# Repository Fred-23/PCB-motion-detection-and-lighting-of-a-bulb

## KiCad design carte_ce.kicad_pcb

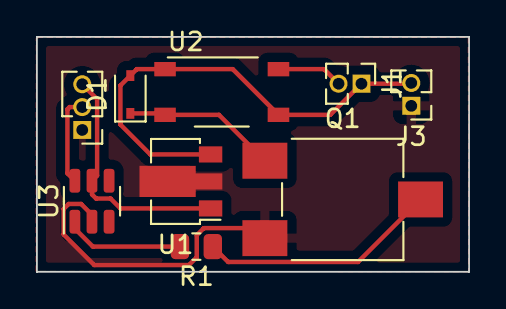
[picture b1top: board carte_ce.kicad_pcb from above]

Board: 2 copper layers, 24.0 x 13.0 mm, 9 parts (0 on the bottom side), 8 nets.

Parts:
 : *; PinHeader_1x03_P1.27mm_Vertical
D1: D_SOD-323
J1, J3: PinHeader_1x02_P1.27mm_Vertical
Q1: Potentiometer_ACP_CA6-VSMD_Vertical
R1: R_0805_2012Metric
U1: SOT-89-3
U2: TLP175A; MFSOP6-4_4.4x3.6mm_P1.27mm
U3: SOT-23-6

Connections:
+9V: D1.2 (A), J1.1, J3.2, U1.3 (IN), U2.1, U2.4
/+5V: .3, U1.1 (OUT), U3.5 (VDD)
Bulb_Supply: J1.2, U2.6
D_mouvement: .2, U3.6 (GP3)
GND: .1, J3.1, Q1.1 (E), U1.2 (GND), U3.2 (VSS)
unnamed: D1.1 (K), Q1.3 (C), U2.3
unnamed: Q1.2 (B), R1.1
unnamed: R1.2, U3.1 (GP0)
